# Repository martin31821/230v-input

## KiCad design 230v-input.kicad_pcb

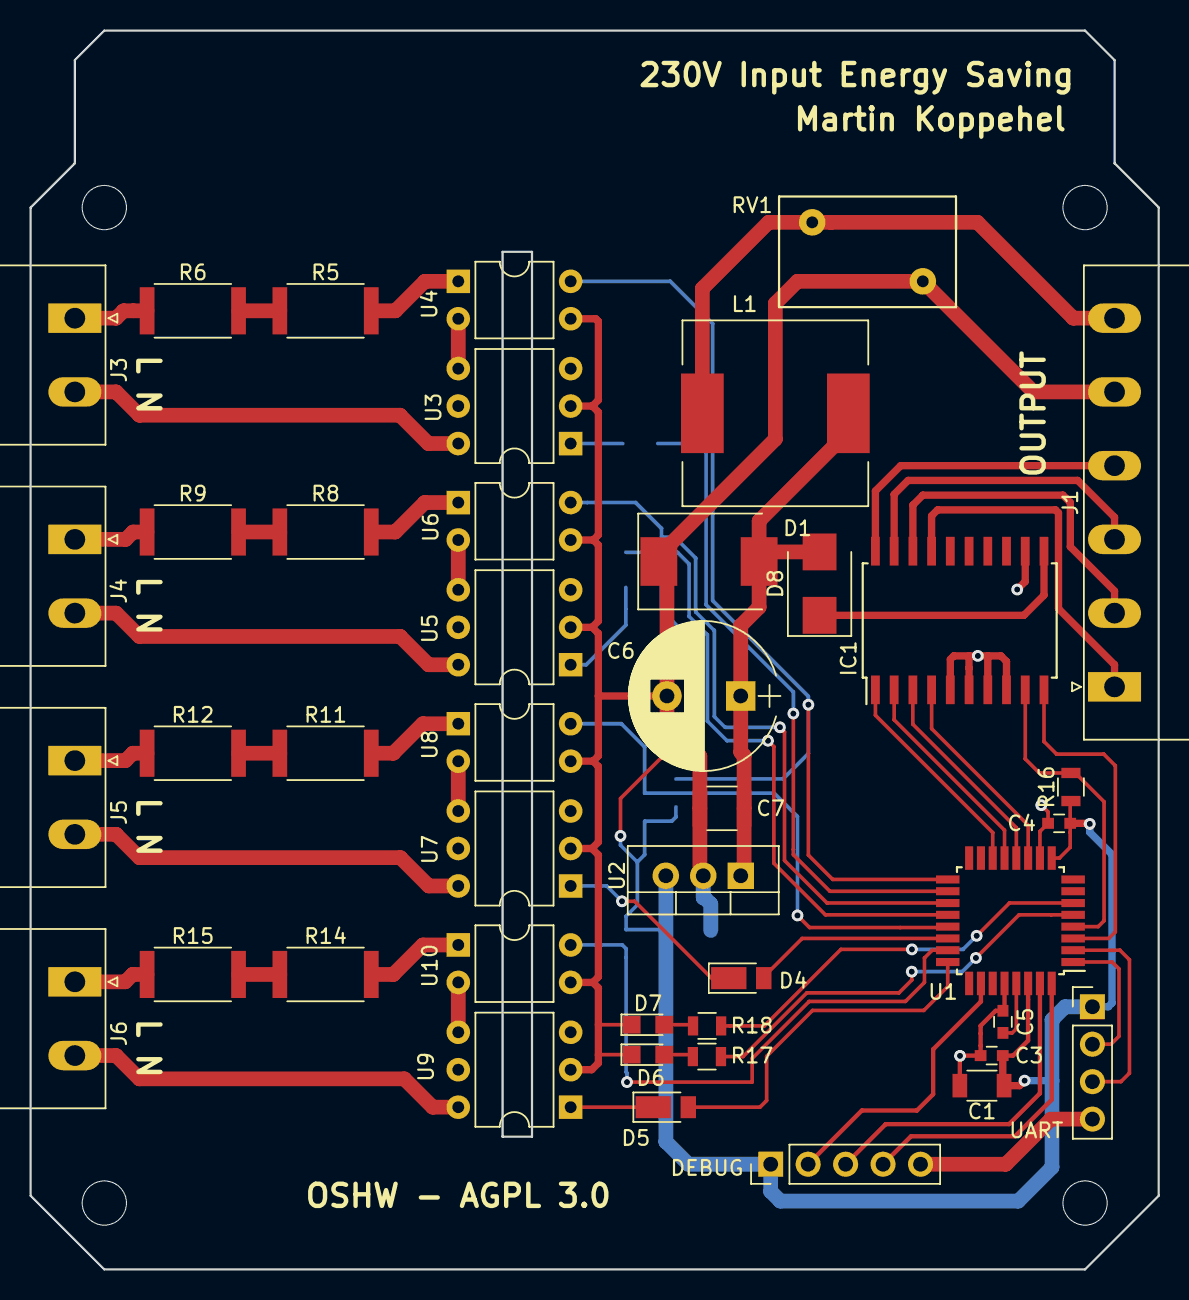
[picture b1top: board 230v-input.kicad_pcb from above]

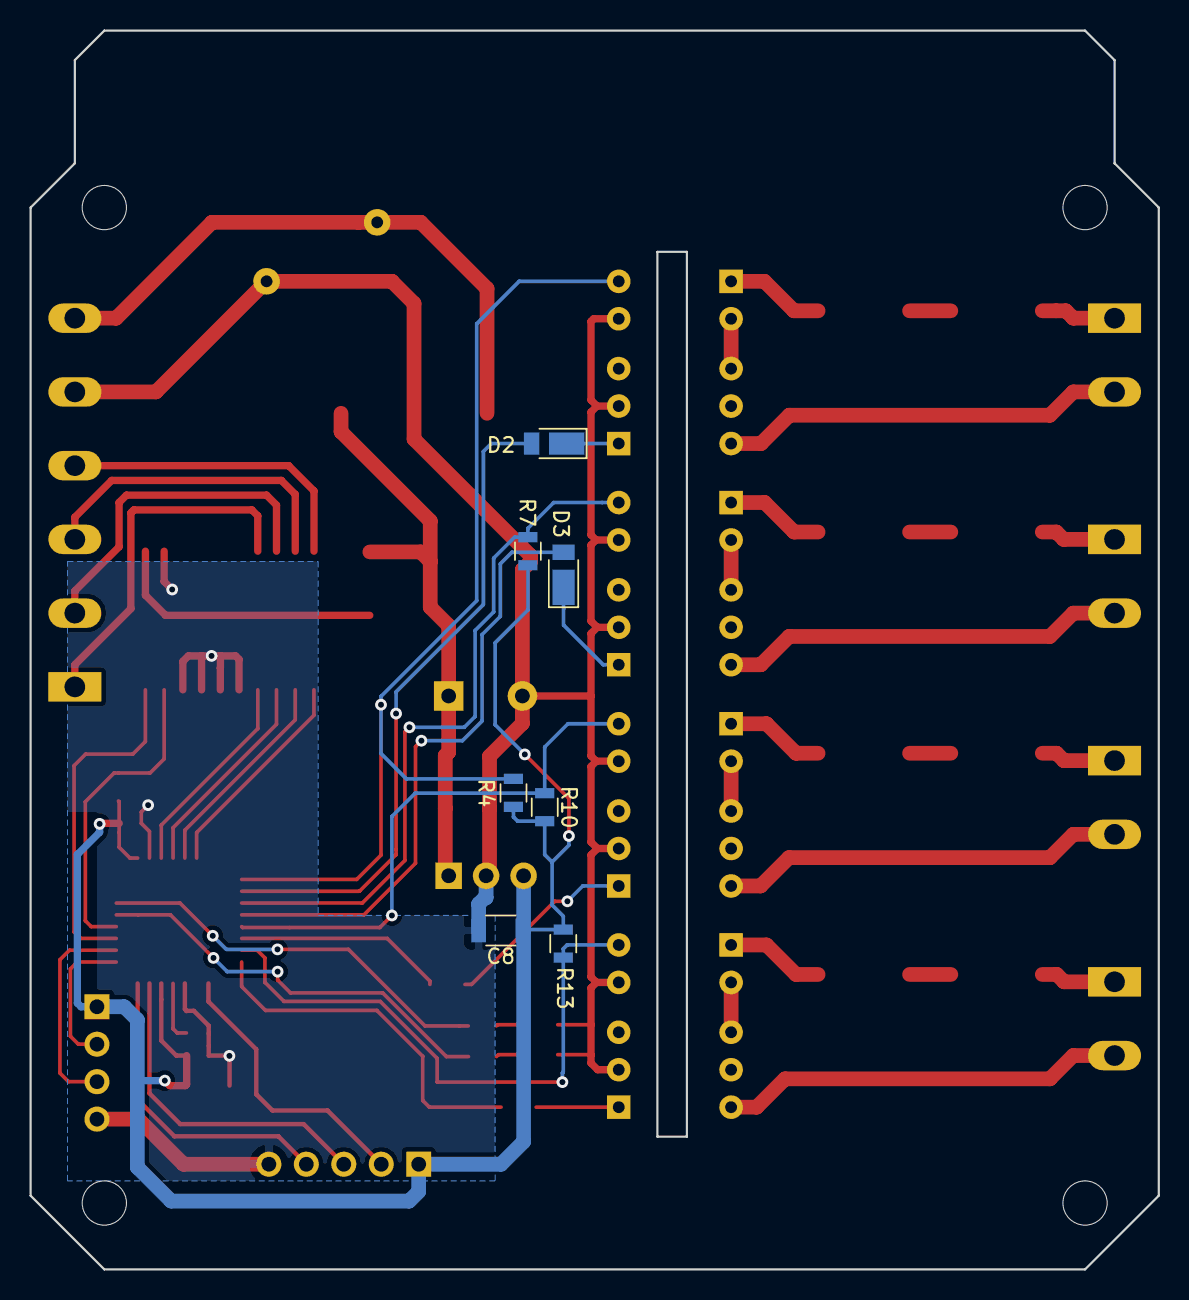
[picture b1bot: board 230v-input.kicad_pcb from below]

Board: 2 copper layers, 76.5 x 84.0 mm, 50 parts (7 on the bottom side), 57 nets.

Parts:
C1, C8: 10µF/10V; C_1206
C3, C4, C5: 100nF; C_0603
C6: 220µF/50V; CP_Radial_D10.0mm_P5.00mm
C7: 10µF/50V; C_1210
D1: 1.5SMCJ30CA; D_SMC
D2, D3, D4, D5: AL5809-15; D_PowerDI-123
D6: LED_RD; LED_0805
D7: LED_GN; LED_0805
D8: STPS3L60U; D_SMB
IC1: UDN2987; SOIC-20W_7.5x12.8mm_Pitch1.27mm
J1: LOGIC_OUT; PhoenixContact_MSTBA-G_06x5.00mm_Angled
J2: DEBUG; Pin_Header_Straight_1x05_Pitch2.54mm
J3, J4, J5, J6: PWR_IN; PhoenixContact_MSTBA-G_02x5.00mm_Angled
J7: UART; Pin_Header_Straight_1x04_Pitch2.54mm
L1: DE1207-82; L_12x12mm_h8mm
R4, R7, R10, R13: 4k7; R_0805
R5, R6, R8, R9, R11, R12, R14, R15: 12k/1W; R_2512
R16: 10k; R_0805
R17, R18: 470; R_0805
RV1: S10K35; RV_Disc_D12_W7.5_P7.5
U1: SAMC20E18A-AU; TQFP-32_7x7mm_Pitch0.8mm
U2: AMSR-7805-NZ; TO-220-3_Vertical
U3, U5, U7, U9: MOC3063M; DIP-6_W7.62mm
U4, U6, U8, U10: LTV-814; DIP-4_W7.62mm

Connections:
+5V: C1.1, C3.1, C4.1, C8.1, J2.1, J7.1, R4.2, R7.2, R10.2, R13.2, R16.1, U1.9, U1.30, U2.3
+24V: C6.1, C7.1, D1.2, D8.2, L1.2, U2.1
/DETECT_A: R4.1, U1.17, U4.4
/DETECT_B: R7.1, U1.19, U6.4
/DETECT_C: R10.1, U1.21, U8.4
/DETECT_D: R13.1, U1.23, U10.4
/FAULT: IC1.9, R16.2, U1.4
/LV_OUT_A: IC1.1, U1.14
/LV_OUT_B: IC1.2, U1.13
/LV_OUT_C: IC1.3, U1.12
/LV_OUT_D: IC1.4, U1.11
/MCU_RESET: J2.2, U1.26
/OUT_RST: IC1.10, U1.3
/SWCLK: J2.3, U1.31
/SWDIO: J2.4, U1.32
/TRIG_A: D2.2, U1.18
/TRIG_B: D3.2, U1.20
/TRIG_C: D4.2, U1.22
/TRIG_D: D5.2, U1.24
/UART_RX: J7.2, U1.1
/UART_TX: J7.3, U1.2
GND: C1.2, C3.2, C4.2, C5.2, C6.2, C7.2, C8.2, D1.1, D6.1, D7.1, IC1.5, IC1.6, IC1.7, IC1.8, IC1.12, J1.5, J2.5, J7.4, RV1.2, U1.10, U1.28, U2.2, U3.2, U4.3, U5.2, U6.3, U7.2, U8.3, U9.2, U10.3
unnamed: C5.1, U1.29
unnamed: D2.1, U3.1
unnamed: D3.1, U5.1
unnamed: D4.1, U7.1
unnamed: D5.1, U9.1
unnamed: D6.2, R17.1
unnamed: D7.2, R18.1
unnamed: D8.1, IC1.11
unnamed: IC1.17, J1.1
unnamed: IC1.18, J1.2
unnamed: IC1.19, J1.3
unnamed: IC1.20, J1.4
unnamed: J3.1, R6.1
unnamed: J3.2, U3.6
unnamed: J4.1, R9.1
unnamed: J4.2, U5.6
unnamed: J5.1, R12.1
unnamed: J5.2, U7.6
unnamed: J6.1, R15.1
unnamed: J6.2, U9.6
unnamed: R5.1, R6.2
unnamed: R5.2, U4.1
unnamed: R8.1, R9.2
unnamed: R8.2, U6.1
unnamed: R11.1, R12.2
unnamed: R11.2, U8.1
unnamed: R14.1, R15.2
unnamed: R14.2, U10.1
unnamed: R17.2, U1.5
unnamed: R18.2, U1.6
unnamed: U3.4, U4.2
unnamed: U5.4, U6.2
unnamed: U7.4, U8.2
unnamed: U9.4, U10.2
VDD: J1.6, L1.1, RV1.1

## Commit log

2018-08-31 Finish first rev
2018-08-31 Adapt to case
2019-02-21 Rev 1
2019-03-02 Rev.2
2019-09-13 License

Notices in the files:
230v-input.kicad_pcb:
OSHW - AGPL 3.0
